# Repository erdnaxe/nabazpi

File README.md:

# NabazPi
The goal of this project is to put a Raspberry Pi in a Nabaztag from Violet.

## Official Nabaztag source
The source code is available [on Google Code](https://code.google.com/archive/p/nabaztag-source-code/).

## Motors
See [motors](motors/) subdirectory.

## RFID detection
In the origial Nabaztag, the RFID is tackled by a **I2C** pcb located under the noze.

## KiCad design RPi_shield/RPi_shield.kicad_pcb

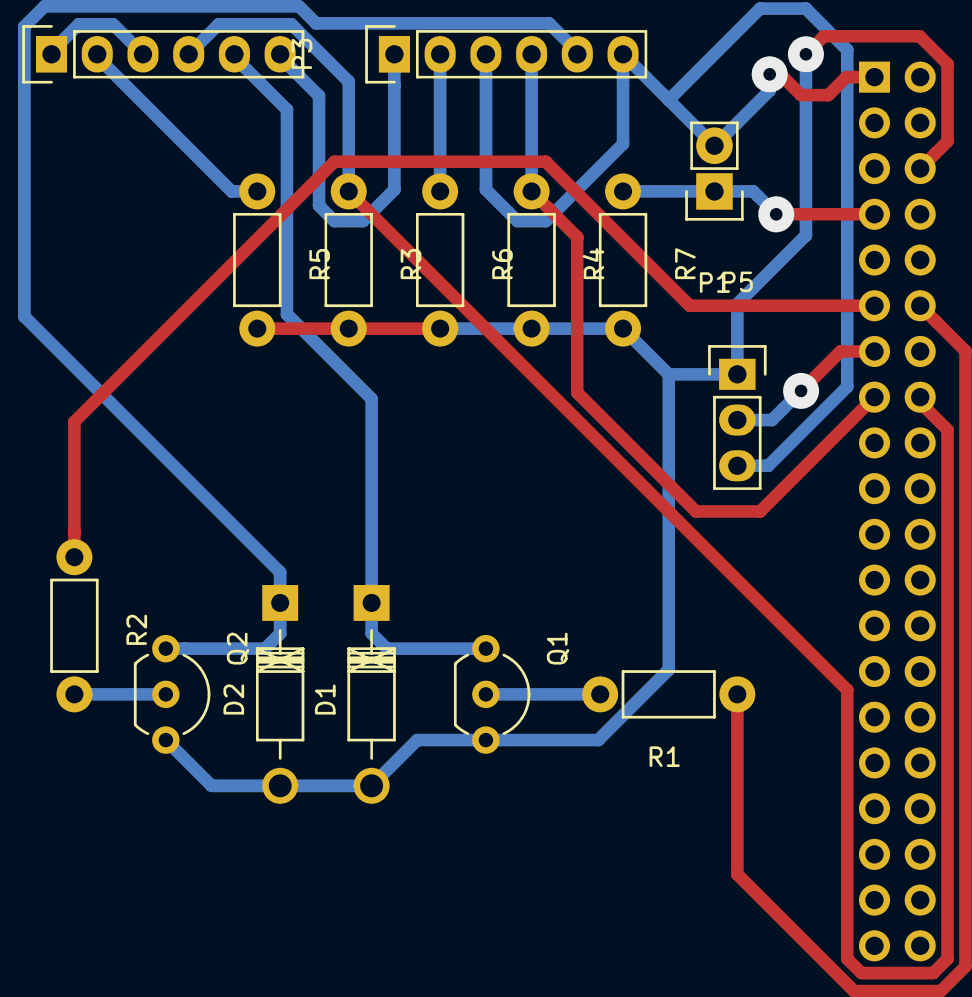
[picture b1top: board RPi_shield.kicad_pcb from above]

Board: 2 copper layers, 16 parts (1 on the bottom side), 14 nets.

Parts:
D1, D2: 1N4001; Diode_DO-41_SOD81_Horizontal_RM10
P1: CONN_BUTTON; Pin_Header_Straight_1x02
P2: CONN_MOT_SEN_L; Pin_Header_Straight_1x06
P3: CONN_MOT_SEN_R; Pin_Header_Straight_1x06
P4: CONN_02X20; Socket_Strip_Straight_2x20
P5: CONN_01X03; Pin_Header_Straight_1x03
Q1, Q2: BC337; TO-92_Inline_Wide
R1, R2, R5, R6: 330; Resistor_Horizontal_RM7mm
R3, R4, R7: 1K; Resistor_Horizontal_RM7mm

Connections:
+3V3: P1.2, P2.1, P2.3, P2.6, P3.1, P3.3, P3.6, P4.1, P5.3
/CATHODE_SEN_L: P2.2, R5.1
/CATHODE_SEN_R: P3.2, R6.1
/COMM_MOT_L: P4.12, R1.1
/COMM_MOT_R: P4.11, R2.1
/EMITTER_SEN_L: P2.4, P4.16, R3.1
/EMITTER_SEN_R: P3.4, P4.15, R4.1
/OUT_BUTTON: P1.1, P4.7, R7.1
/OUT_MOT_L: D1.1, P2.5, Q1.1
/OUT_MOT_R: D2.1, P3.5, Q2.1
/POT: P4.13, P5.2
GND: D1.2, D2.2, P4.6, P5.1, Q1.3, Q2.3, R3.2, R4.2, R5.2, R6.2, R7.2
unnamed: Q1.2, R1.2
unnamed: Q2.2, R2.2

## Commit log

2016-12-25 Init motor doc
2016-12-25 Add GPIO scripts
2016-12-25 Add audio dir
2016-12-26 Update kicad files
2016-12-27 Clean......
2016-12-27 Routage in progress
2016-12-27 Plop
